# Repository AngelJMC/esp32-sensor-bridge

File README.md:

# 4-20ma-wifi-bridge

## Features
### Hardware
 * 5-24v Power supply.
 * 1 Input 4-20 mA.
 * 2 Relays to control loads up to 1A at 24DVC or 0.5A at 125VAC.
 * WIFI 802.11 b/g/n (2.4 GHz), up to 150 Mbps.

## Get the source code
Download repository and update submodules:

```
$ git clone https://github.com/AngelJMC/4-20ma-wifi-bridge.git
```

### Directory Structure

    .
    ├── docs          # Documentation files
    ├── firmware      # FW source code (Visual Studio Code)
    ├── hardware      # HW design files (Kicad)

## Firmware

If you want to modify the source code or program your devices, it is highly recommended to use Visual Studio Code and the Platformio plugin. Just open the "firmware" directory with Visual Studio Code and the whole project will be ready for use.

### Load firmware 

 1. Build and Upload Filesystem Image.
 2. Build and Upload program code.

## Configuration Process

 1. Build and Upload Filesystem Image to your ESP32
 2. Build and Upload program code.
 3. Connect mobile or PC with hotspot: Logger_4-20mA_XXXX. Password: Vd4WD619Uemi
 4. Go to web browser and hit 192.168.4.1. Use the credential admin/Y32Pv9RY to enter.
 5. Go to Network section and scan for your wifi network, write password and static network configuration if you want, hit apply.
 6. Go to Service section give necessary server credential for MQTT and set the pub/sub topic names.
 7. Go to Other section if you need calibrate the 4-20mA acquisition electronic.

## Configuration Web

## Library Used

* ESp32_arduino :- https://github.com/espressif/arduino-esp32
* ESPAsyncWebServer:- https://github.com/me-no-dev/ESPAsyncWebServer
* AsyncTCP:- https://github.com/me-no-dev/AsyncTCP
* esp32 SPIFF File system :- https://github.com/me-no-dev/arduino-esp32fs-plugin

The configuration web page is based on the work of @futechiot https://github.com/futechiot/Configuration-webpage-esp32

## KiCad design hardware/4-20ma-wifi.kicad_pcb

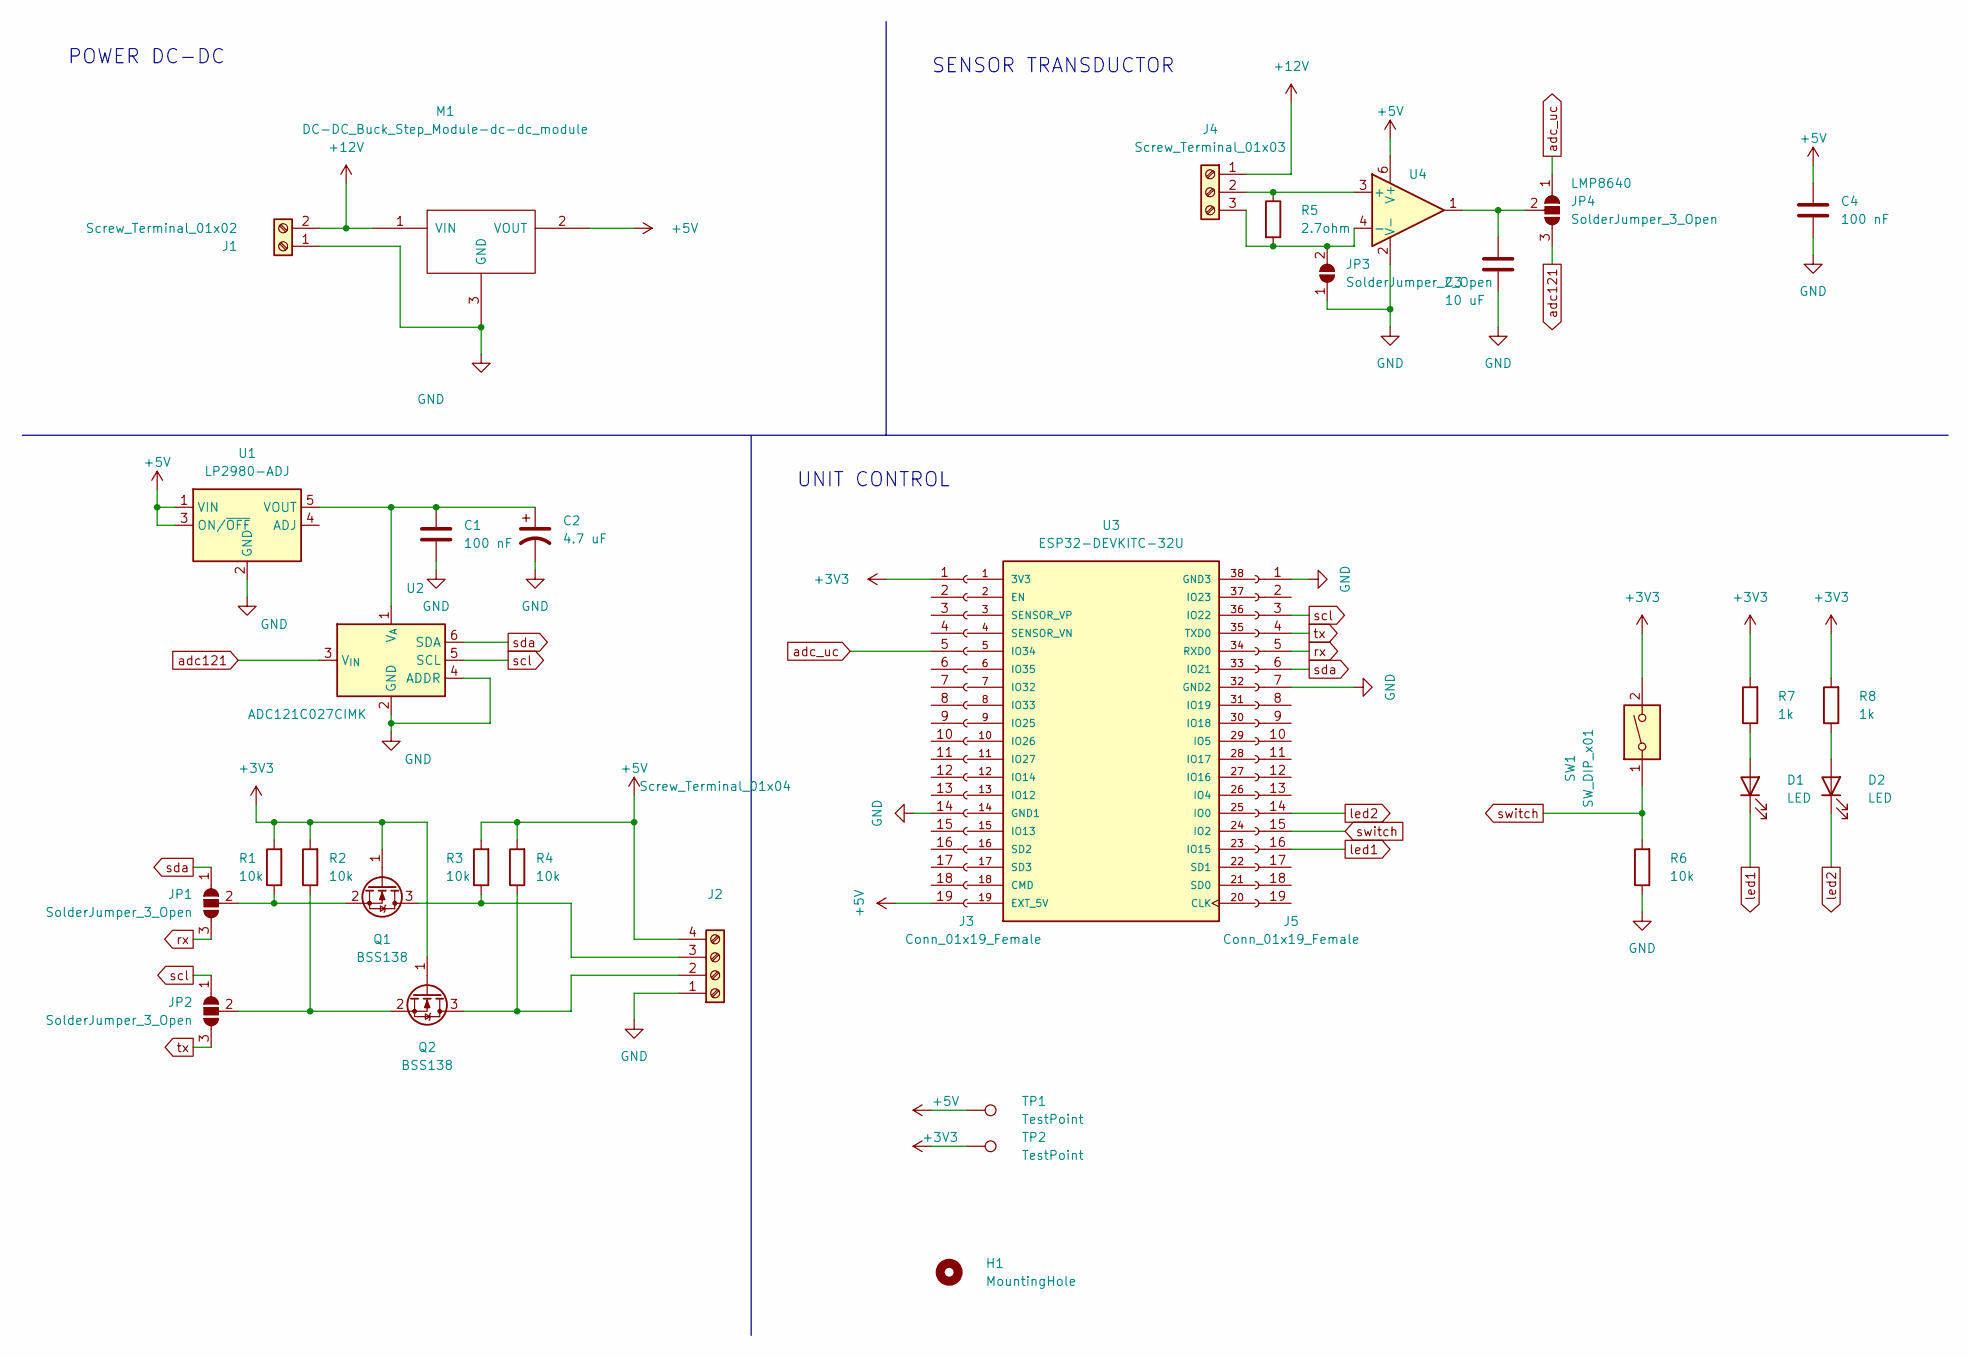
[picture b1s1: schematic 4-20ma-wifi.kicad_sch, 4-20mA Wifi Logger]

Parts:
C1, C4: 100 nF; C_0805_2012Metric_Pad1.18x1.45mm_HandSolder
C2: 4.7 uF; CP_EIA-3216-18_Kemet-A
C3: 10 uF; C_0805_2012Metric_Pad1.18x1.45mm_HandSolder
D1, D2: LED; LED_D1.8mm_W1.8mm_H2.4mm_Horizontal_O1.27mm_Z1.6mm
H1: MountingHole; MountingHole_2.7mm_M2.5_ISO7380_Pad
J1: Screw_Terminal_01x02; TerminalBlock__1x02_P5.00mm_90Degree
J2: Screw_Terminal_01x04; TerminalBlock__1x04_P5.00mm_90Degree
J3, J5: Conn_01x19_Female; PinSocket_1x19_P2.54mm_Vertical
J4: Screw_Terminal_01x03; TerminalBlock__1x03_P5.00mm_90Degree
JP1, JP2, JP4: SolderJumper_3_Open; SolderJumper-3_P1.3mm_Open_RoundedPad1.0x1.5mm
JP3: SolderJumper_2_Open; SolderJumper-2_P1.3mm_Open_Pad1.0x1.5mm
M1: DC-DC_Buck_Step_Module-dc-dc_module; DC-DC_Buck_Step_Module
Q1, Q2: BSS138; SOT-23
R1, R2, R3, R4, R6: 10k; R_0805_2012Metric_Pad1.20x1.40mm_HandSolder
R5: 2.7ohm; R_2512_6332Metric_Pad1.40x3.35mm_HandSolder
R7, R8: 1k; R_0805_2012Metric_Pad1.20x1.40mm_HandSolder
SW1: SW_DIP_x01; SW_Tactile_SPST_Angled_PTS645Vx58-2LFS
TP1, TP2: TestPoint; TestPoint_Pad_D1.0mm
U1: LP2980-ADJ; SOT-23-5
U2: ADC121C027CIMK; SOT-23-6
U3: ESP32-DEVKITC-32U; MODULE_ESP32-DEVKITC-32U; PARTREV N/A
U4: LMP8640; SOT-23-6

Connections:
+3V3: J3.1, Q1.1 (G), Q2.1 (G), R1.2, R2.2, R7.2, R8.2, SW1.2, TP2.1
+5V: C4.1, J2.4, J3.19, M1.2 (VOUT), R3.2, R4.2, TP1.1, U1.1 (VIN), U1.3 (ON/~OFF), U4.6 (V+)
+12V: J1.2, J4.1, M1.1 (VIN)
GND: C1.2, C2.2, C3.2, C4.2, J1.1, J2.1, J3.14, J5.1, J5.7, JP3.1 (A), M1.3 (GND), R6.1, U1.2 (GND), U2.2 (GND), U2.4 (ADDR), U4.2 (V-)
unnamed: C1.1, C2.1, U1.5 (VOUT), U2.1 (V_{A})
unnamed: C3.1, JP4.2 (C), U4.1
unnamed: D1.2 (A), R7.1
unnamed: D2.2 (A), R8.1
unnamed: J2.2, Q2.3 (D), R4.1
unnamed: J2.3, Q1.3 (D), R3.1
unnamed: J4.2, R5.1, U4.3 (+)
unnamed: J4.3, JP3.2 (B), R5.2, U4.4 (-)
unnamed: JP1.2 (C), Q1.2 (S), R1.1
unnamed: JP2.2 (C), Q2.2 (S), R2.1
adc121: JP4.3 (B), U2.3 (V_{IN})
adc_uc: J3.5, JP4.1 (A)
led1: D1.1 (K), J5.16
led2: D2.1 (K), J5.14
rx: J5.5, JP1.3 (B)
scl: J5.3, JP2.1 (A), U2.5 (SCL)
sda: J5.6, JP1.1 (A), U2.6 (SDA)
switch: J5.15, R6.2, SW1.1
tx: J5.4, JP2.3 (B)

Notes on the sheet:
UNIT CONTROL
SENSOR TRANSDUCTOR
POWER DC-DC

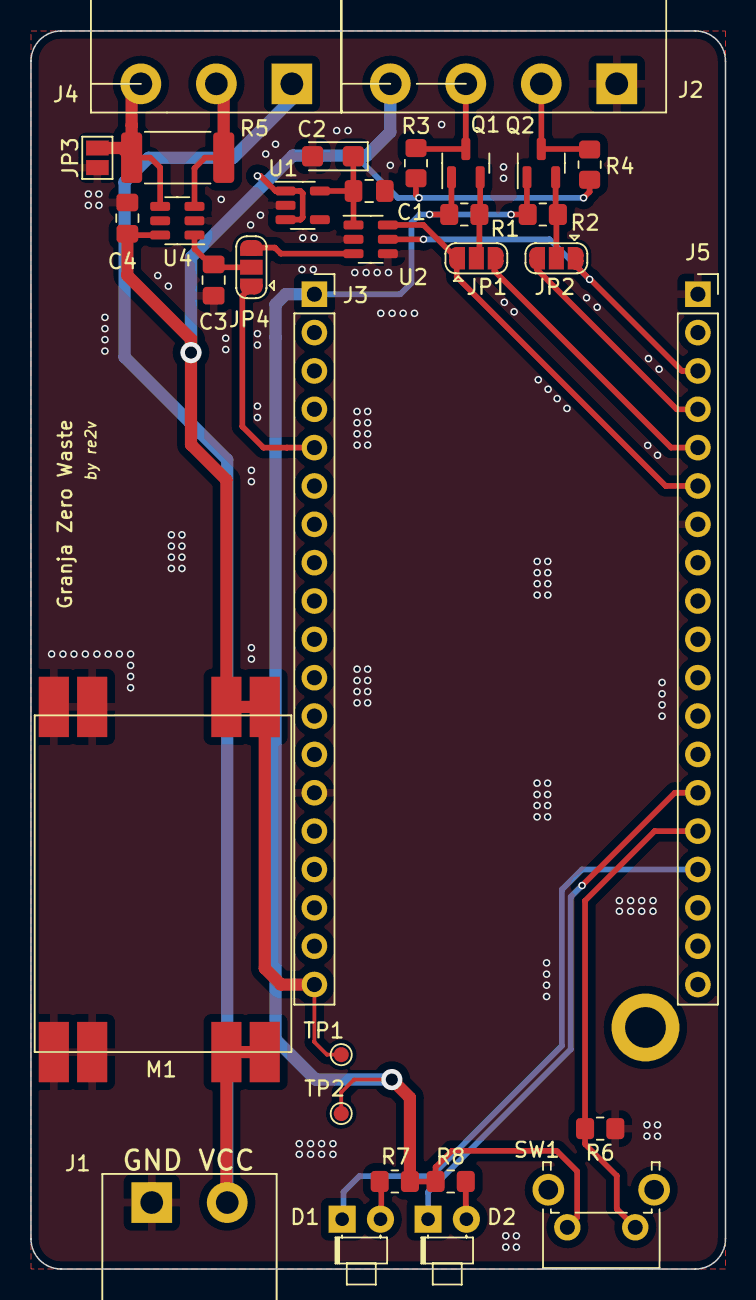
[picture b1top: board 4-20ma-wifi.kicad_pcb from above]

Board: 2 copper layers, 46.0 x 82.0 mm, 33 parts (0 on the bottom side), 23 nets.

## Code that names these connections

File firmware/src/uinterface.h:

/*
    Project: <https://github.com/AngelJMC/4-20ma-wifi-bridge>   
    Copyright (c) 2022 Angel Maldonado <angelgesus@gmail.com>. 
    Licensed under the MIT License: <http://opensource.org/licenses/MIT>.
    SPDX-License-Identifier: MIT 
*/

#ifndef __U_INTERFACE__
#define __U_INTERFACE__

#include "stdint.h"

#define LED_OFF 0x1
#define LED_ON 0x0

enum {  
    RELAY1 = 26, 
    RELAY2 = 27,
    SENS   = 34,
    LED1   = 0,
    LED2   = 15,
    SWITCH = 2 
};

/*Led status modes*/
enum modes {
    OFF = 0,
    BLINK = 1,
    ON = 2
};

/**
 * @brief Initialize the leds controls */
void interface_init( void );

/**
 * @brief Set the state of the led used as Mode indicator (RED)
 * @param mode, the state of the led: OFF, BLINK, ON */
void interface_setMode( enum modes mode );

/**
 * @brief Set the state of the led used as State indicator (GREEN)
 * @param mode, the state of the led: OFF, BLINK, ON */
void interface_setState( enum modes mode );

/**
 * @brief This function reads some ADC acquisitions and return the filtered value. */
int board_getadcValue( void );

void board_initadc( void );

/**
 * @brief This function does a factory reset of the device. */
void factoryreset( void );

#endif //__U_INTERFACE__ 

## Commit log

2022-09-18 Added firmware source
2022-09-18 Added electronic schematic and layout
2022-09-18 Added documentation
2022-09-20 Work around PCB design. Added ADC121 to the schematic
2022-09-22 Work around PCB design
    - Added new terminal block to connect usar or i2c device
    - Added shift-level to 3.3 - 5v usart/i2c
    - Work around layout
2022-09-25 Work around pcb layout
2022-09-26 Added LP2980 Dropout regulator to power the ADC converter
2022-09-28 Minor changes - prepare release
2022-10-02 Work around mqtt messages
2022-10-10 Work around front-end and backend apis
2022-10-22 Added adc121 driver
2022-10-22 Added support to SHT2X and ADC121. Modifies json frame.
2022-10-23 Fixes minor issues
2022-10-24 Add calibration ranges to the measurement struct
2022-10-30 Added json-maker submodule
2022-10-30 Minor fixes
2022-10-30 Naming refactor
2022-10-30 Changes the default wifi password
2022-11-02 Fix bug related to info mqtt topic
2022-11-05 Improve software timer use to pulish MQTT
2022-11-09 Improves reconnections
2022-11-25 Modified 0-20mA to ppm conversion
2025-01-15 Removed FreeRTOS include to avoid build problems.
2025-01-15 Improve readability
2025-06-08 Added UDP user configuration: flash config and web server
2025-06-08 Added ld2410 sensor task processing.
2025-06-08 WIP - Added udp sending
